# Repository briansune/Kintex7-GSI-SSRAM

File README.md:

# Kintex7-GSI-SSRAM

This is a NBT(No Bus turn around) pipeline/flow through Synchronous SRAM example.

The SRAM chip is using the GSI 3V3 standard 36bit sram with 18 bit address 2 busrt address bit.

Here is one of the Vivado ILA capture.

Have fun =] ~

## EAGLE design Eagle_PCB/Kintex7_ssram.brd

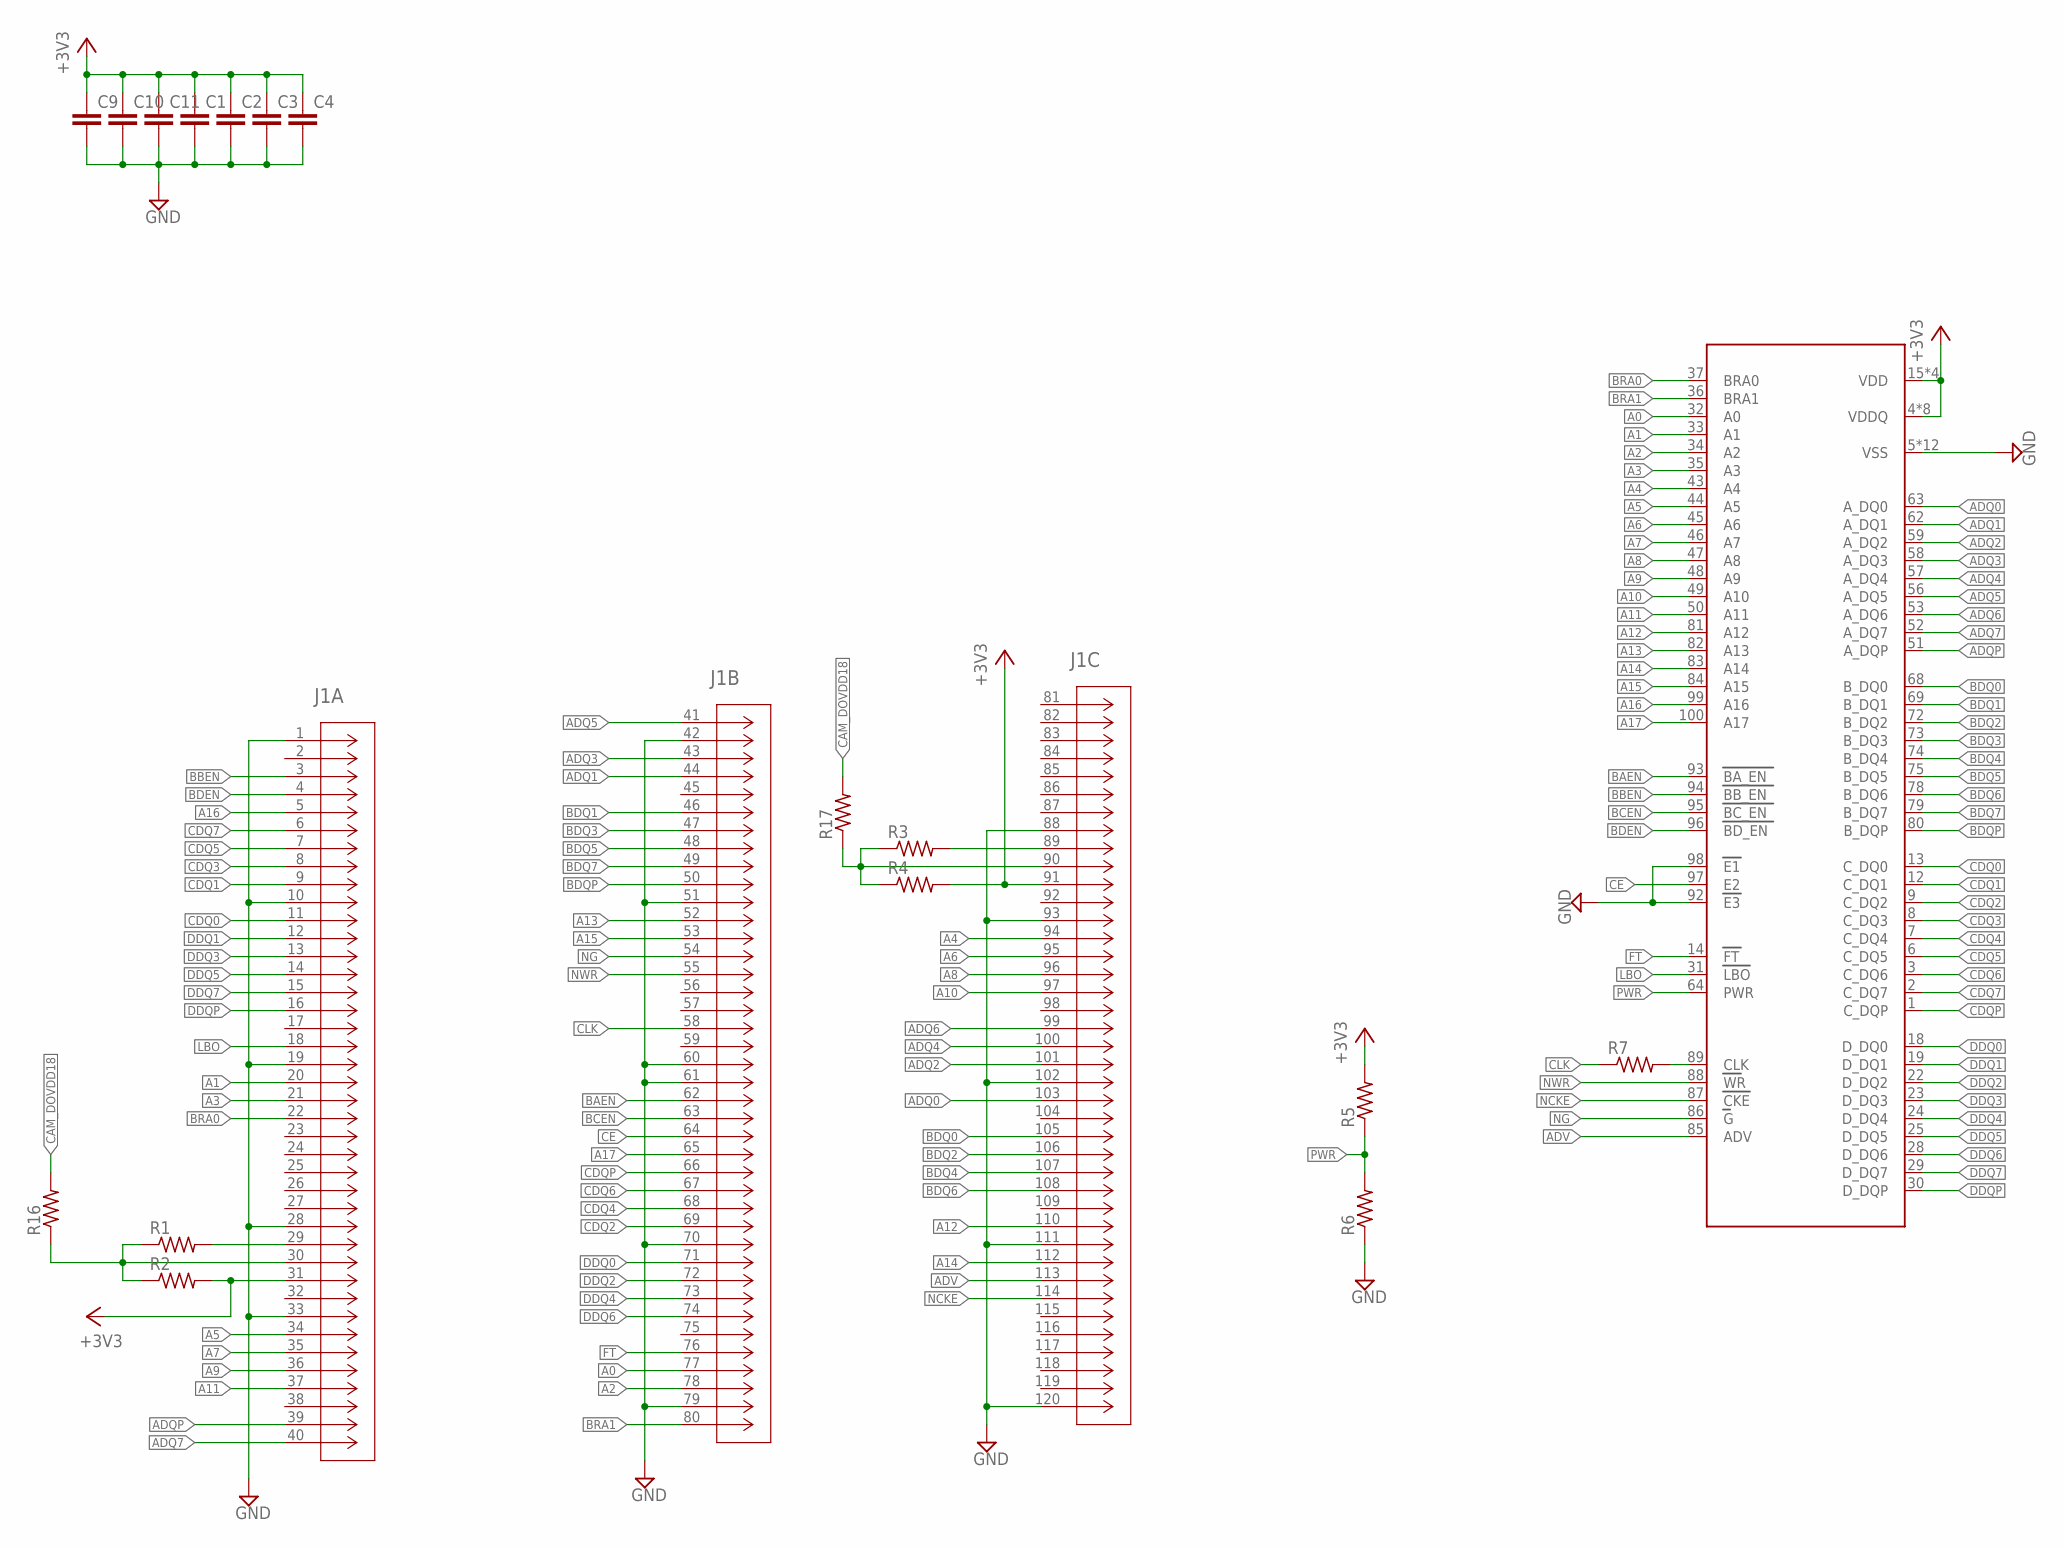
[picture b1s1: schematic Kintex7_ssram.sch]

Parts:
C1, C2, C3, C4, C9, C10, C11: C-EUC0603; C0603
J1: 5177985-5; CONN_5177985-5
R1, R2, R3, R4, R16, R17: R-US_R0805; R0805
R5, R6, R7: R-US_R0603; R0603
RAM: GS8320Z36GTSMT; TQFP100-R

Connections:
+3V3: C1.1, C2.1, C3.1, C4.1, C9.1, C10.1, C11.1, J1.31, J1.91, R2.2, R4.2, R5.2, RAM.4 (VDDQ), RAM.11 (VDDQ), RAM.15 (VDD), RAM.20 (VDDQ), RAM.27 (VDDQ), RAM.41 (VDD), RAM.54 (VDDQ), RAM.61 (VDDQ), RAM.65 (VDD), RAM.70 (VDDQ), RAM.77 (VDDQ), RAM.91 (VDD)
A0: J1.77, RAM.32 (A0)
A1: J1.20, RAM.33 (A1)
A2: J1.78, RAM.34 (A2)
A3: J1.21, RAM.35 (A3)
A4: J1.94, RAM.43 (A4)
A5: J1.34, RAM.44 (A5)
A6: J1.95, RAM.45 (A6)
A7: J1.35, RAM.46 (A7)
A8: J1.96, RAM.47 (A8)
A9: J1.36, RAM.48 (A9)
A10: J1.97, RAM.49 (A10)
A11: J1.37, RAM.50 (A11)
A12: J1.110, RAM.81 (A12)
A13: J1.52, RAM.82 (A13)
A14: J1.112, RAM.83 (A14)
A15: J1.53, RAM.84 (A15)
A16: J1.5, RAM.99 (A16)
A17: J1.65, RAM.100 (A17)
ADQ0: J1.103, RAM.63 (A_DQ0)
ADQ1: J1.44, RAM.62 (A_DQ1)
ADQ2: J1.101, RAM.59 (A_DQ2)
ADQ3: J1.43, RAM.58 (A_DQ3)
ADQ4: J1.100, RAM.57 (A_DQ4)
ADQ5: J1.41, RAM.56 (A_DQ5)
ADQ6: J1.99, RAM.53 (A_DQ6)
ADQ7: J1.40, RAM.52 (A_DQ7)
ADQP: J1.39, RAM.51 (A_DQP)
ADV: J1.113, RAM.85 (ADV)
BAEN: J1.62, RAM.93 (BA_EN)
BBEN: J1.3, RAM.94 (BB_EN)
BCEN: J1.63, RAM.95 (BC_EN)
BDEN: J1.4, RAM.96 (BD_EN)
BDQ0: J1.105, RAM.68 (B_DQ0)
BDQ1: J1.46, RAM.69 (B_DQ1)
BDQ2: J1.106, RAM.72 (B_DQ2)
BDQ3: J1.47, RAM.73 (B_DQ3)
BDQ4: J1.107, RAM.74 (B_DQ4)
BDQ5: J1.48, RAM.75 (B_DQ5)
BDQ6: J1.108, RAM.78 (B_DQ6)
BDQ7: J1.49, RAM.79 (B_DQ7)
BDQP: J1.50, RAM.80 (B_DQP)
BRA0: J1.22, RAM.37 (BRA0)
BRA1: J1.80, RAM.36 (BRA1)
CAM_DOVDD18: R16.2, R17.2
CDQ0: J1.11, RAM.13 (C_DQ0)
CDQ1: J1.9, RAM.12 (C_DQ1)
CDQ2: J1.69, RAM.9 (C_DQ2)
CDQ3: J1.8, RAM.8 (C_DQ3)
CDQ4: J1.68, RAM.7 (C_DQ4)
CDQ5: J1.7, RAM.6 (C_DQ5)
CDQ6: J1.67, RAM.3 (C_DQ6)
CDQ7: J1.6, RAM.2 (C_DQ7)
CDQP: J1.66, RAM.1 (C_DQP)
CE: J1.64, RAM.97 (E2)
CLK: J1.58, R7.1
DDQ0: J1.71, RAM.18 (D_DQ0)
DDQ1: J1.12, RAM.19 (D_DQ1)
DDQ2: J1.72, RAM.22 (D_DQ2)
DDQ3: J1.13, RAM.23 (D_DQ3)
DDQ4: J1.73, RAM.24 (D_DQ4)
DDQ5: J1.14, RAM.25 (D_DQ5)
DDQ6: J1.74, RAM.28 (D_DQ6)
DDQ7: J1.15, RAM.29 (D_DQ7)
DDQP: J1.16, RAM.30 (D_DQP)
FT: J1.76, RAM.14 (FT)
GND: C1.2, C2.2, C3.2, C4.2, C9.2, C10.2, C11.2, J1.1, J1.10, J1.19, J1.28, J1.33, J1.42, J1.51, J1.60, J1.61, J1.70, J1.79, J1.88, J1.93, J1.102, J1.111, J1.120, R6.1, RAM.5 (VSS), RAM.10 (VSS), RAM.17 (VSS), RAM.21 (VSS), RAM.26 (VSS), RAM.40 (VSS), RAM.55 (VSS), RAM.60 (VSS), RAM.67 (VSS), RAM.71 (VSS), RAM.76 (VSS), RAM.90 (VSS), RAM.92 (E3), RAM.98 (E1)
LBO: J1.18, RAM.31 (LBO)
unnamed: R7.2, RAM.89 (CLK)
unnamed: J1.90, R3.1, R4.1, R17.1
unnamed: J1.29, R1.2
unnamed: J1.89, R3.2
unnamed: J1.30, R1.1, R2.1, R16.1
NCKE: J1.114, RAM.87 (CKE)
NG: J1.54, RAM.86 (G)
NWR: J1.55, RAM.88 (WR)
PWR: R5.1, R6.2, RAM.64 (PWR)

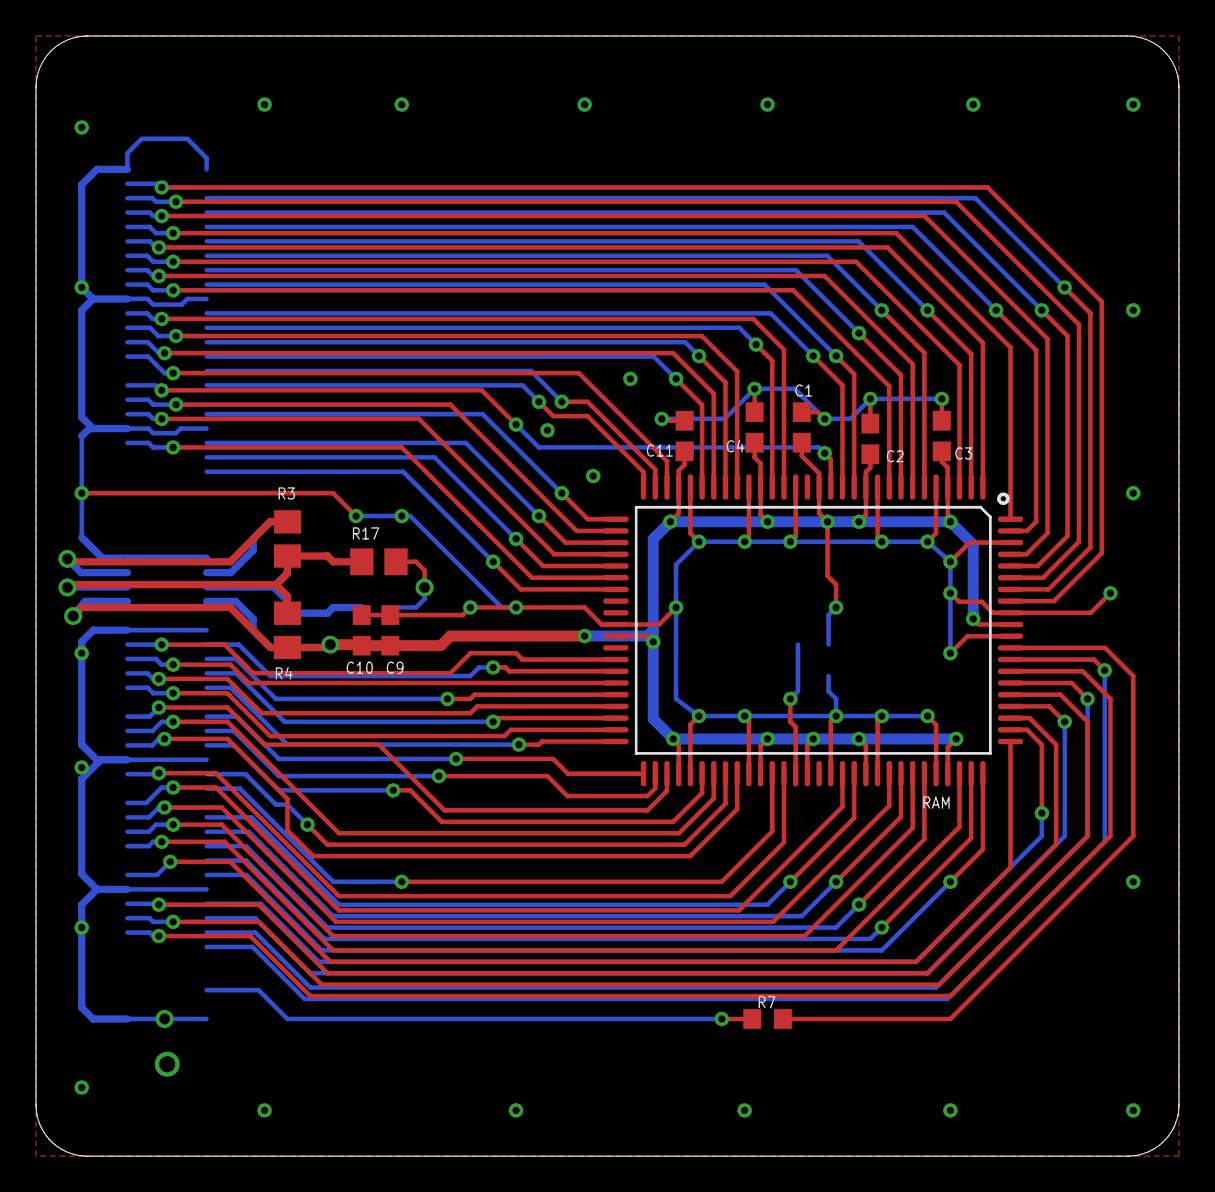
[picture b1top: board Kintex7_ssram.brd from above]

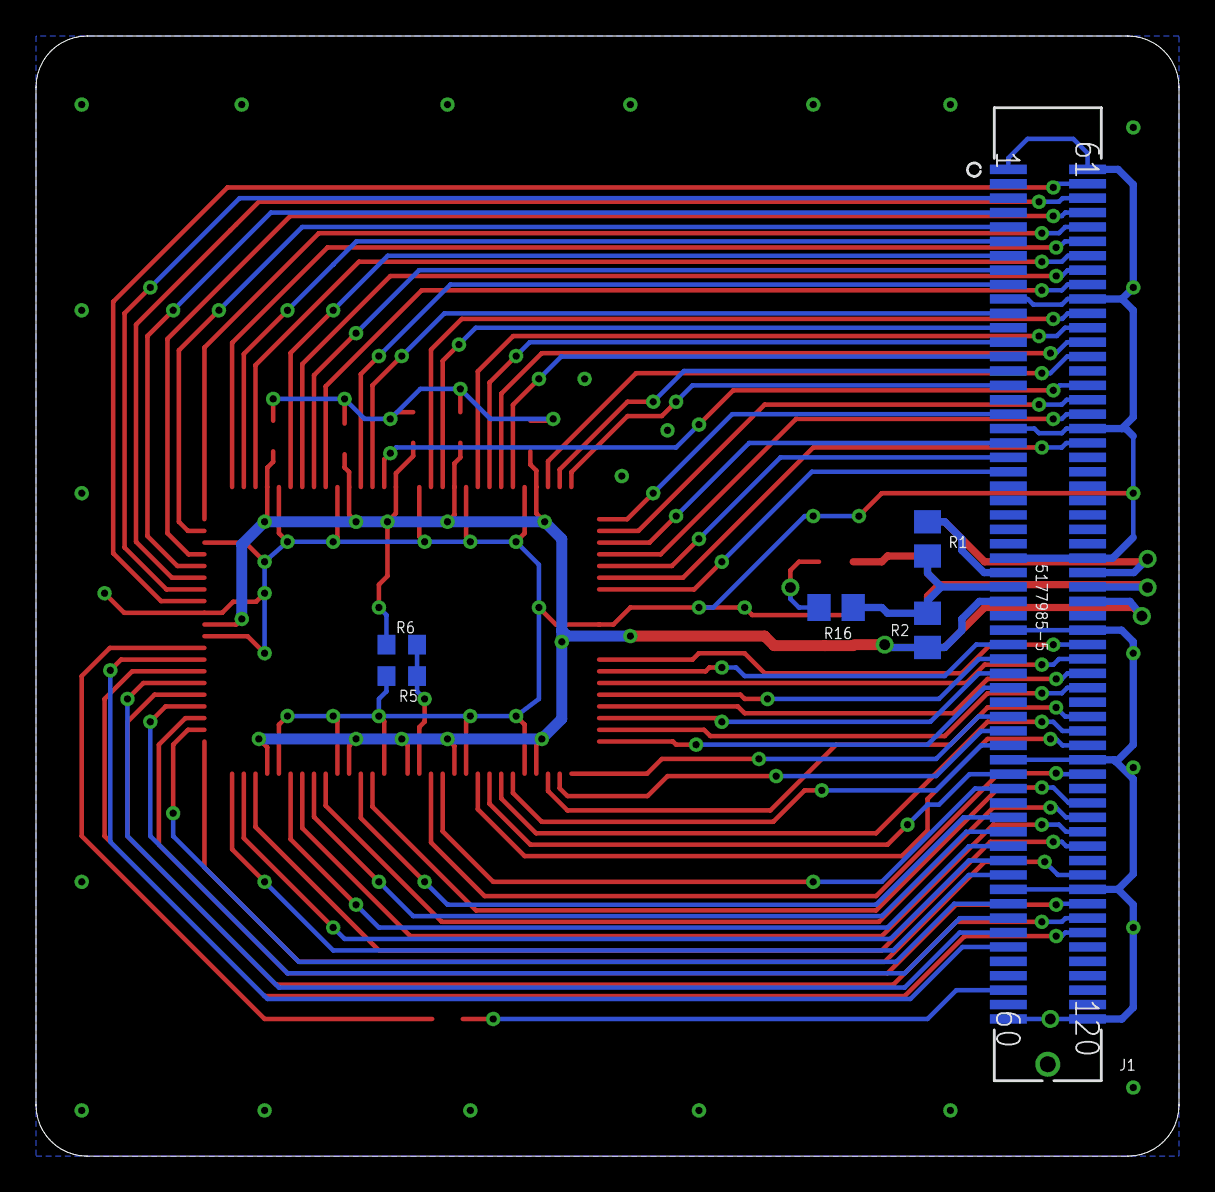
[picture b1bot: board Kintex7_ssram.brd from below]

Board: 2 copper layers, 63.5 x 62.2 mm, 18 parts (6 on the bottom side), 77 nets.

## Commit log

2020-05-06 Create LICENSE
2020-05-06 datasheet
